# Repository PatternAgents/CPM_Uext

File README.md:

CPM Uext Adaptor
====================

PatternAgents CPM Uext Adaptor

[  
*PatternAgents CPM Uext Adaptor*](http://www.patternagents.com/projects/CPM_Uext.html)

The "CPM Uext Adaptor" board is designed to enable Cypress PSoC development boards to utilize Uext peripherals.

The PatternAgents "CPM Uext Adaptor" board supports :

Cypress CY8CKIT-001 : (Supports up to three (3) "CPM Uext Adaptor")

Cypress CY8CKIT-030 : (Supports up to two (2) "CPM Uext Adaptor")

Cypress CY8CKIT-050 : (Supports up to two (2) "CPM Uext Adaptor")

Cypress CY3280-28xxx : (Supports one (1) "CPM Uext Adaptor")

Cypress CY3280-22x45 : (Supports one (1) "CPM Uext Adaptor")

(Not an Exhaustive list as more Cypress development boards are routinely released)

For information on Uext peripherals, see http://en.wikipedia.org/wiki/UEXT

[  
*Licensing CC BY-NC-SA 4.0*](http://creativecommons.org/licenses/by-nc-sa/4.0/)

PatternAgents uses the increasingly popular business model called "Dual Licensing" 
in which both the open source software distribution mechanism and traditional commercial software distribution models are combined.

Open Source Projects:        

If you are developing and distributing open source applications under the Creative Commons CC BY-NC-SA 4.0, 
as published by the Creative Commons Foundation, then you are free to use the PatternAgents hardware/software under the CC BY-NC-SA 4.0 license. 
Please note that CC BY-NC-SA 4.0 requires that all modifications to the original code as well as all Derivative Works 
must also be released under the terms of the CC BY-NC-SA 4.0 license.

Closed Source Projects:

If you are developing and distributing traditional closed source or commercial applications, 
you must purchase a PatternAgents commercial use license, 
which is specifically designed for users interested in retaining the proprietary status of their designs and code. 
All PatternAgents commercial licenses expressly supersede the CC BY-NC-SA 4.0 license. 
This means that when you license the PatternAgents software under a commercial license, 
you specifically do not use the software under the CC BY-NC-SA 4.0 license and therefore you are not subject to any of its terms.
        
If you would like to use our designs for your own personal or educational use, have at it! 

Our public design repository is available at <a href="https://github.com/patternagents">Github</a>.

If you would like to produce our designs for commercial use, or as products for sale, 
please contact us to arrange for a Commercial Use license. We have many other designs, 
as well as options and extras that are not released publicly. 
We will also customize designs, firmware, and software for a reasonable fee, just contact us to discuss your requirements.

THIS SOFTWARE IS PROVIDED BY THE CONTRIBUTORS "AS IS" AND WITHOUT ANY EXPRESS OR IMPLIED WARRANTIES, 
INCLUDING, BUT NOT LIMITED TO, THE IMPLIED WARRANTIES OF MERCHANTABILITY AND FITNESS FOR A PARTICULAR PURPOSE ARE DISCLAIMED. 
IN NO EVENT SHALL THE COPYRIGHT OWNER OR CONTRIBUTORS BE LIABLE FOR ANY DIRECT, INDIRECT, INCIDENTAL, SPECIAL, EXEMPLARY, 
OR CONSEQUENTIAL DAMAGES (INCLUDING, BUT NOT LIMITED TO, PROCUREMENT OF SUBSTITUTE GOODS OR SERVICES; LOSS OF USE, DATA, 
OR PROFITS; OR BUSINESS INTERRUPTION) HOWEVER CAUSED AND ON ANY THEORY OF LIABILITY, WHETHER IN CONTRACT, 
STRICT LIABILITY, OR TORT (INCLUDING NEGLIGENCE OR OTHERWISE) ARISING IN ANY WAY OUT OF THE USE OF THIS SOFTWARE, 
EVEN IF ADVISED OF THE POSSIBILITY OF SUCH DAMAGE. 

-------------------------------------------------------------------------------------------

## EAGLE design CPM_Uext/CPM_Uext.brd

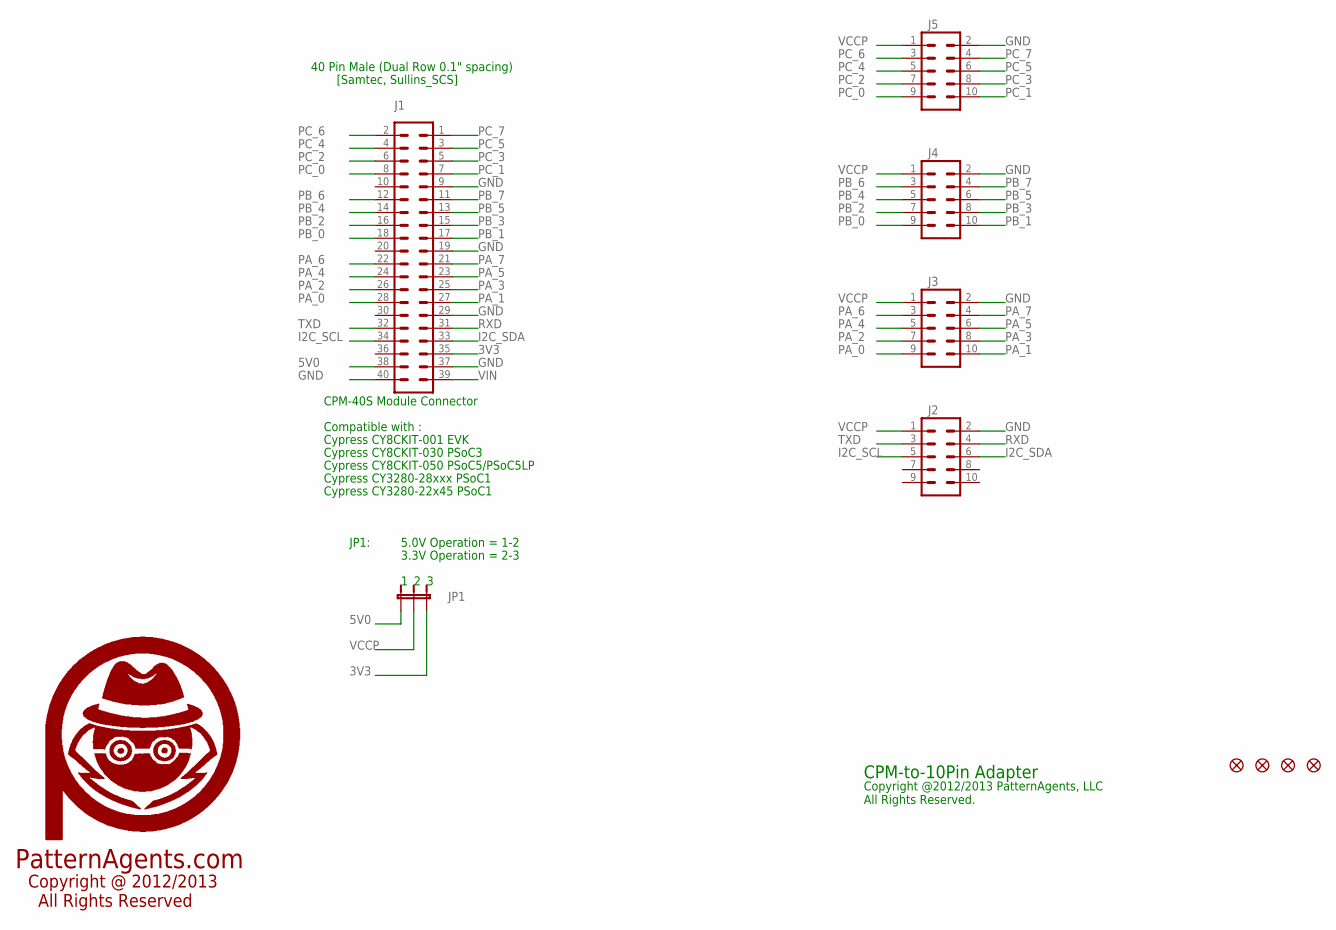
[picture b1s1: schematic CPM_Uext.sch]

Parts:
J1: SULLINS_SCS; MA20-2
J2, J3, J4, J5: M05X2; 2X5-UEXT
JP1: JUMPER-3PTH; 1X03
JP2, JP3, JP4, JP5: FIDUCIAL1.5X3; FIDUCIAL-1.5X3
U$1: LOGO_PA_AGENTLARGE; LOGO_PA_AGENT_LARGE

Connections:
3V3: J1.35, JP1.3
5V0: J1.38, JP1.1
GND: J1.9, J1.19, J1.29, J1.37, J1.40, J2.2, J3.2, J4.2, J5.2
I2C_SCL: J1.34, J2.5
I2C_SDA: J1.33, J2.6
PA_0: J1.28, J3.9
PA_1: J1.27, J3.10
PA_2: J1.26, J3.7
PA_3: J1.25, J3.8
PA_4: J1.24, J3.5
PA_5: J1.23, J3.6
PA_6: J1.22, J3.3
PA_7: J1.21, J3.4
PB_0: J1.18, J4.9
PB_1: J1.17, J4.10
PB_2: J1.16, J4.7
PB_3: J1.15, J4.8
PB_4: J1.14, J4.5
PB_5: J1.13, J4.6
PB_6: J1.12, J4.3
PB_7: J1.11, J4.4
PC_0: J1.8, J5.9
PC_1: J1.7, J5.10
PC_2: J1.6, J5.7
PC_3: J1.5, J5.8
PC_4: J1.4, J5.5
PC_5: J1.3, J5.6
PC_6: J1.2, J5.3
PC_7: J1.1, J5.4
RXD: J1.31, J2.4
TXD: J1.32, J2.3
VCCP: J2.1, J3.1, J4.1, J5.1, JP1.2
VIN: J1.39

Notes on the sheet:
[Samtec, Sullins_SCS]
40 Pin Male (Dual Row 0.1" spacing)
CPM-40S Module Connector
Compatible with :
Cypress CY8CKIT-001 EVK
Cypress CY8CKIT-030 PSoC3
Cypress CY3280-28xxx PSoC1
Cypress CY3280-22x45 PSoC1
Cypress CY8CKIT-050 PSoC5/PSoC5LP
JP1:
5.0V Operation = 1-2
3.3V Operation = 2-3
PatternAgents.com
Copyright @ 2012/2013 All Rights Reserved
CPM-to-10Pin Adapter
Copyright @2012/2013 PatternAgents, LLC All Rights Reserved.

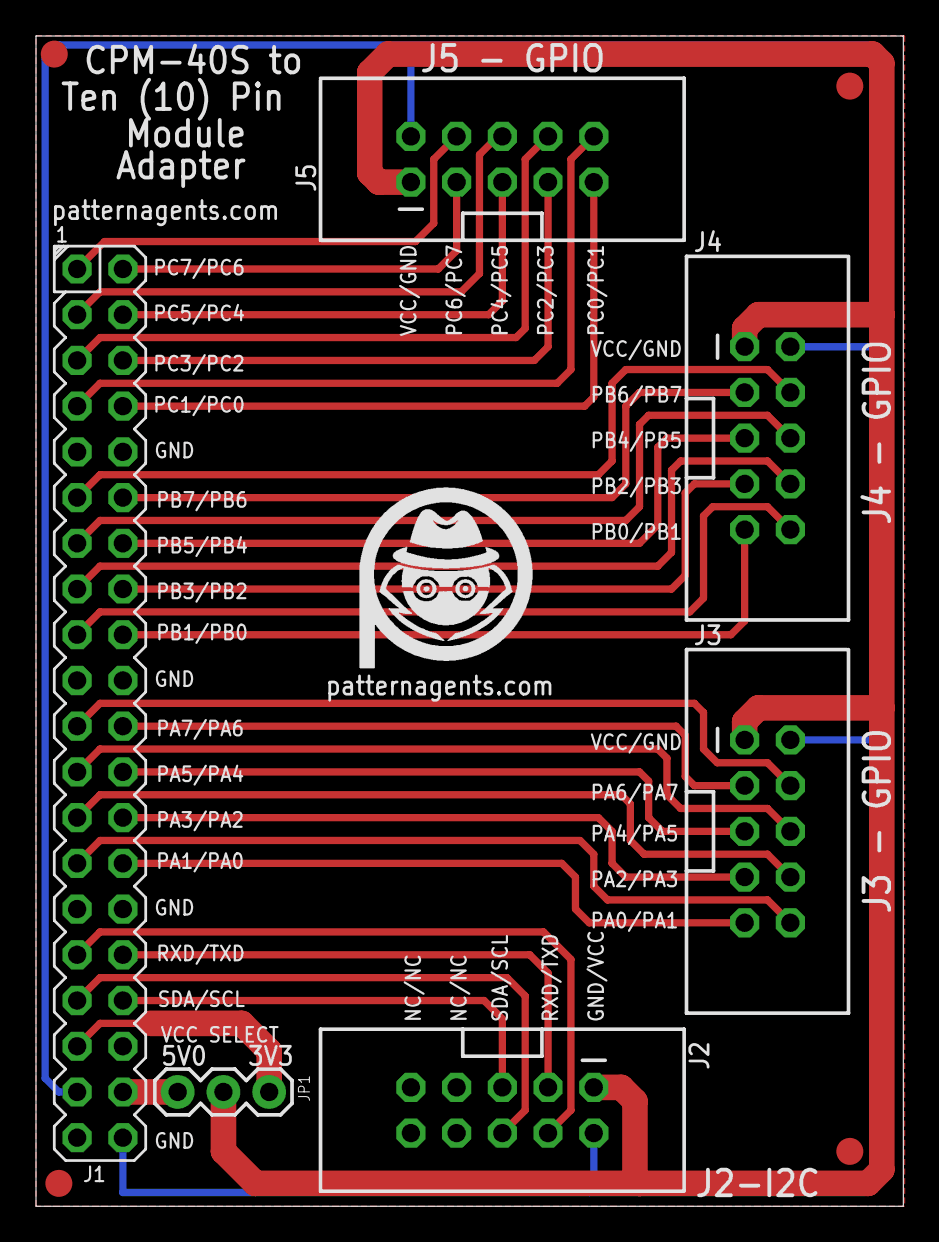
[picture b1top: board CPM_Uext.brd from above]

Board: 2 copper layers, 48.2 x 65.0 mm, 12 parts (1 on the bottom side), 32 nets.

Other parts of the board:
U$3: LOGO_PA_AGENTLARGE; LOGO_PA_AGENT_LARGE

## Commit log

2013-07-17 initial check-in
2013-07-18 add Eagle design files
2013-07-18 epf update
2013-07-19 link fixes
2013-07-19 link fixes/typo
2013-07-22 reduce png file sizes
2013-12-23 Move licensing to CC 4.0

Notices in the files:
parts and their libraries:
SparkFun: Licensing: CC v3.0 Share-Alike You are welcome to use this library for commercial purposes.
